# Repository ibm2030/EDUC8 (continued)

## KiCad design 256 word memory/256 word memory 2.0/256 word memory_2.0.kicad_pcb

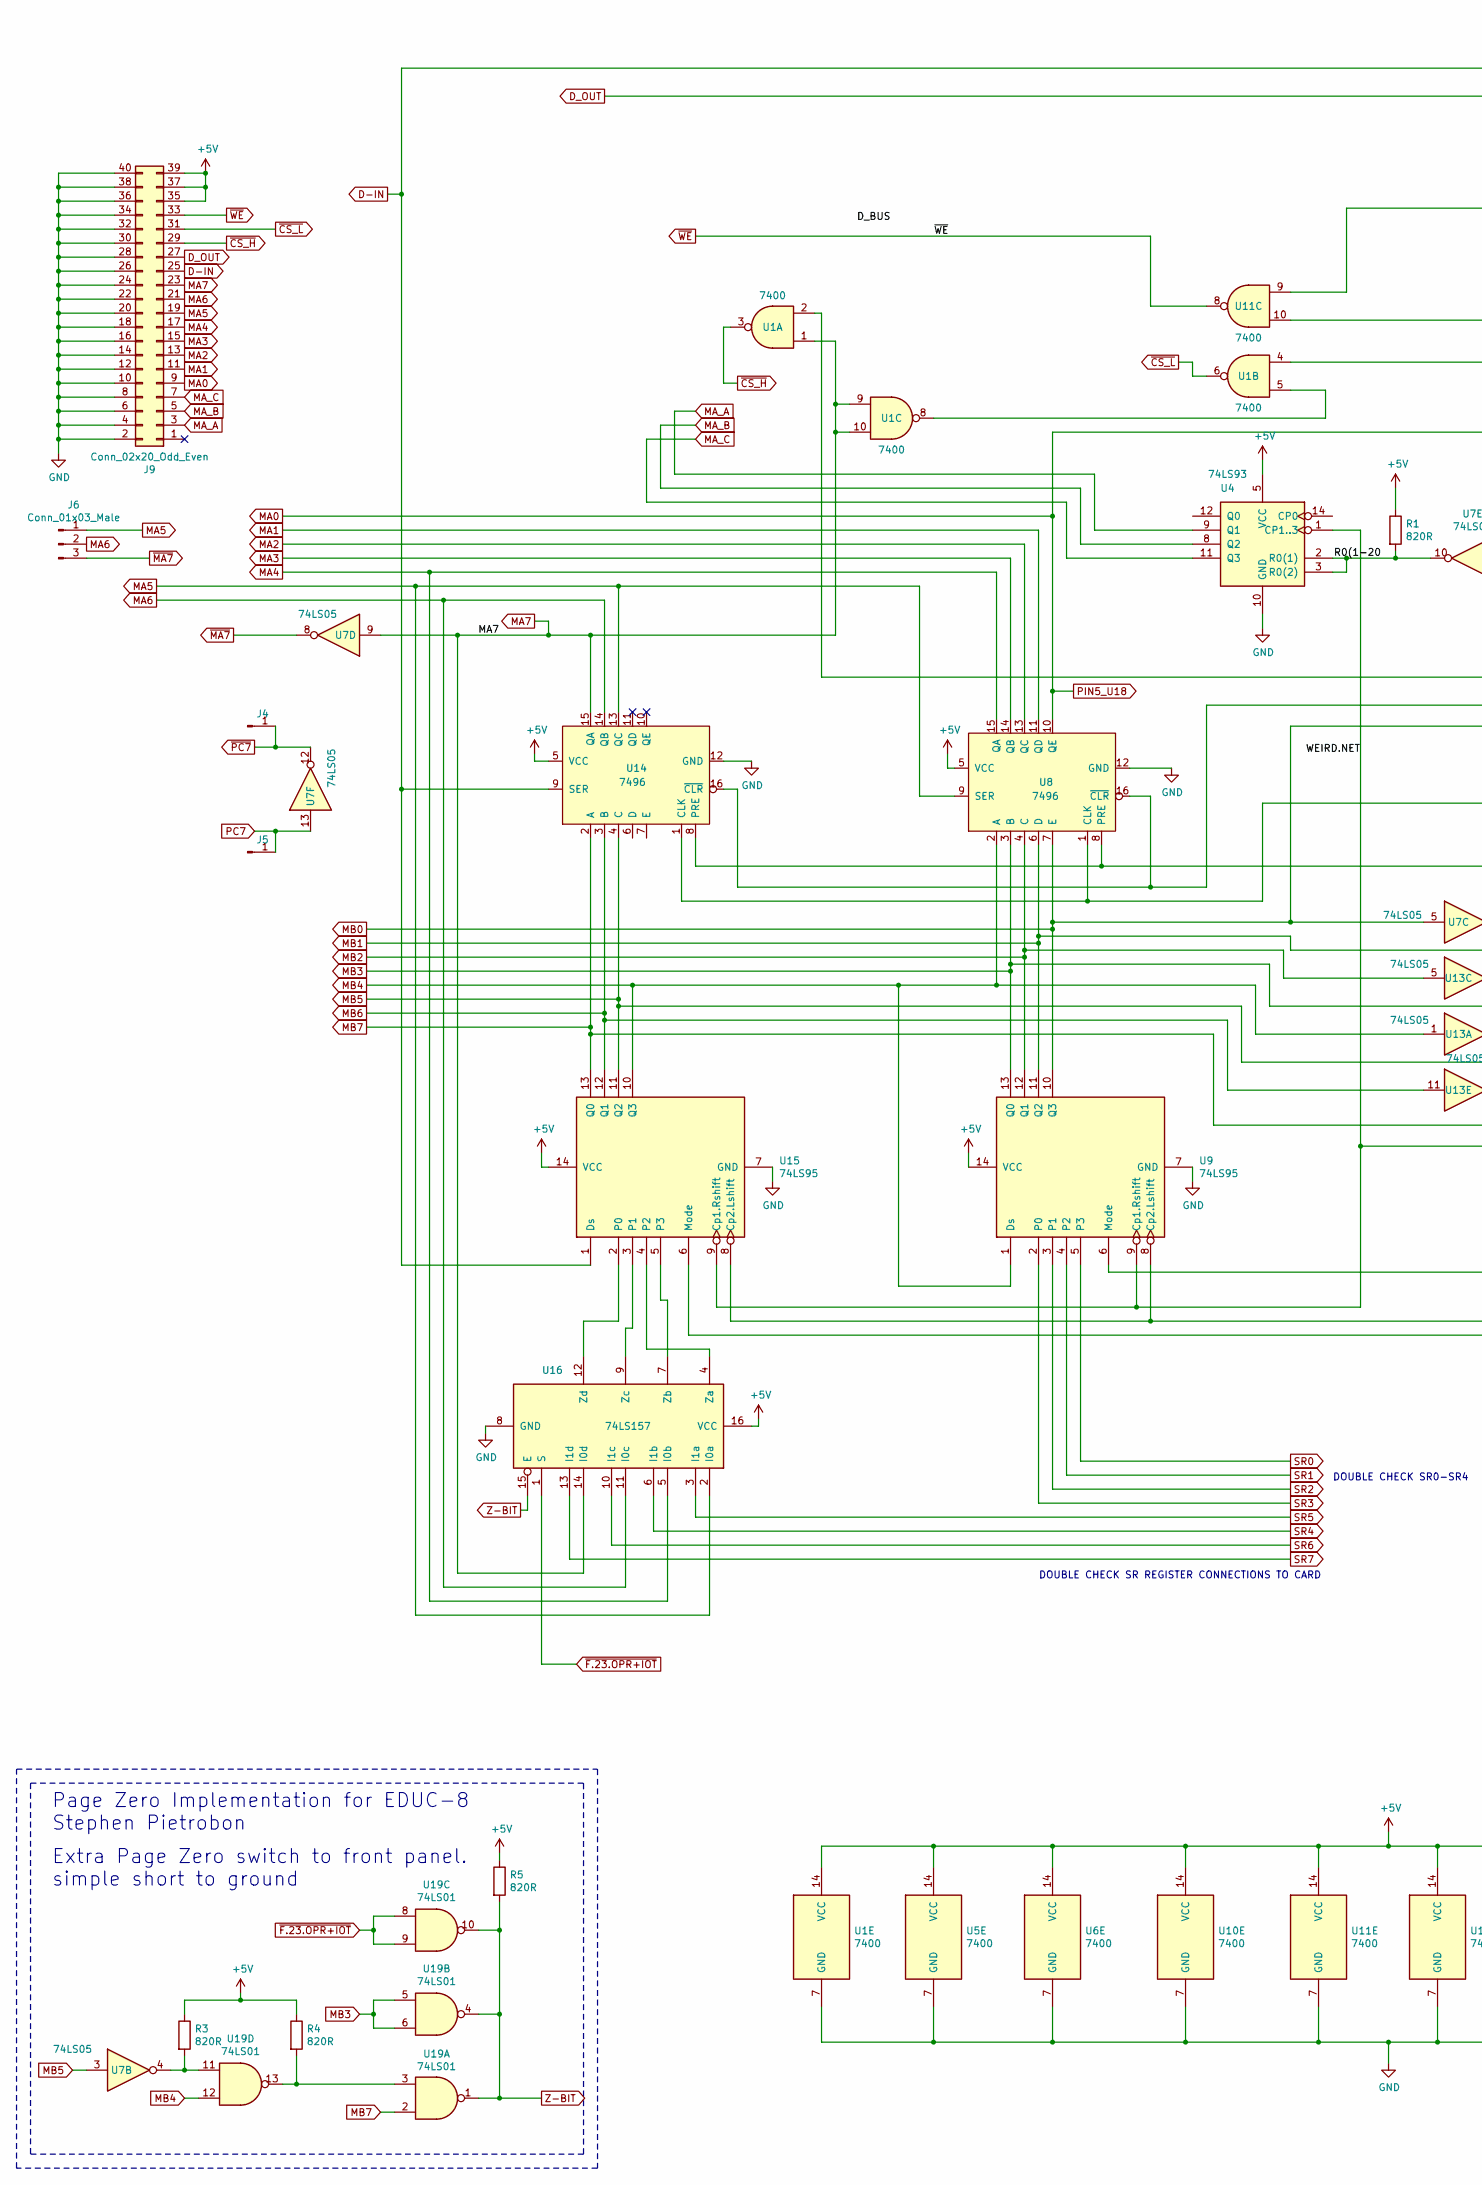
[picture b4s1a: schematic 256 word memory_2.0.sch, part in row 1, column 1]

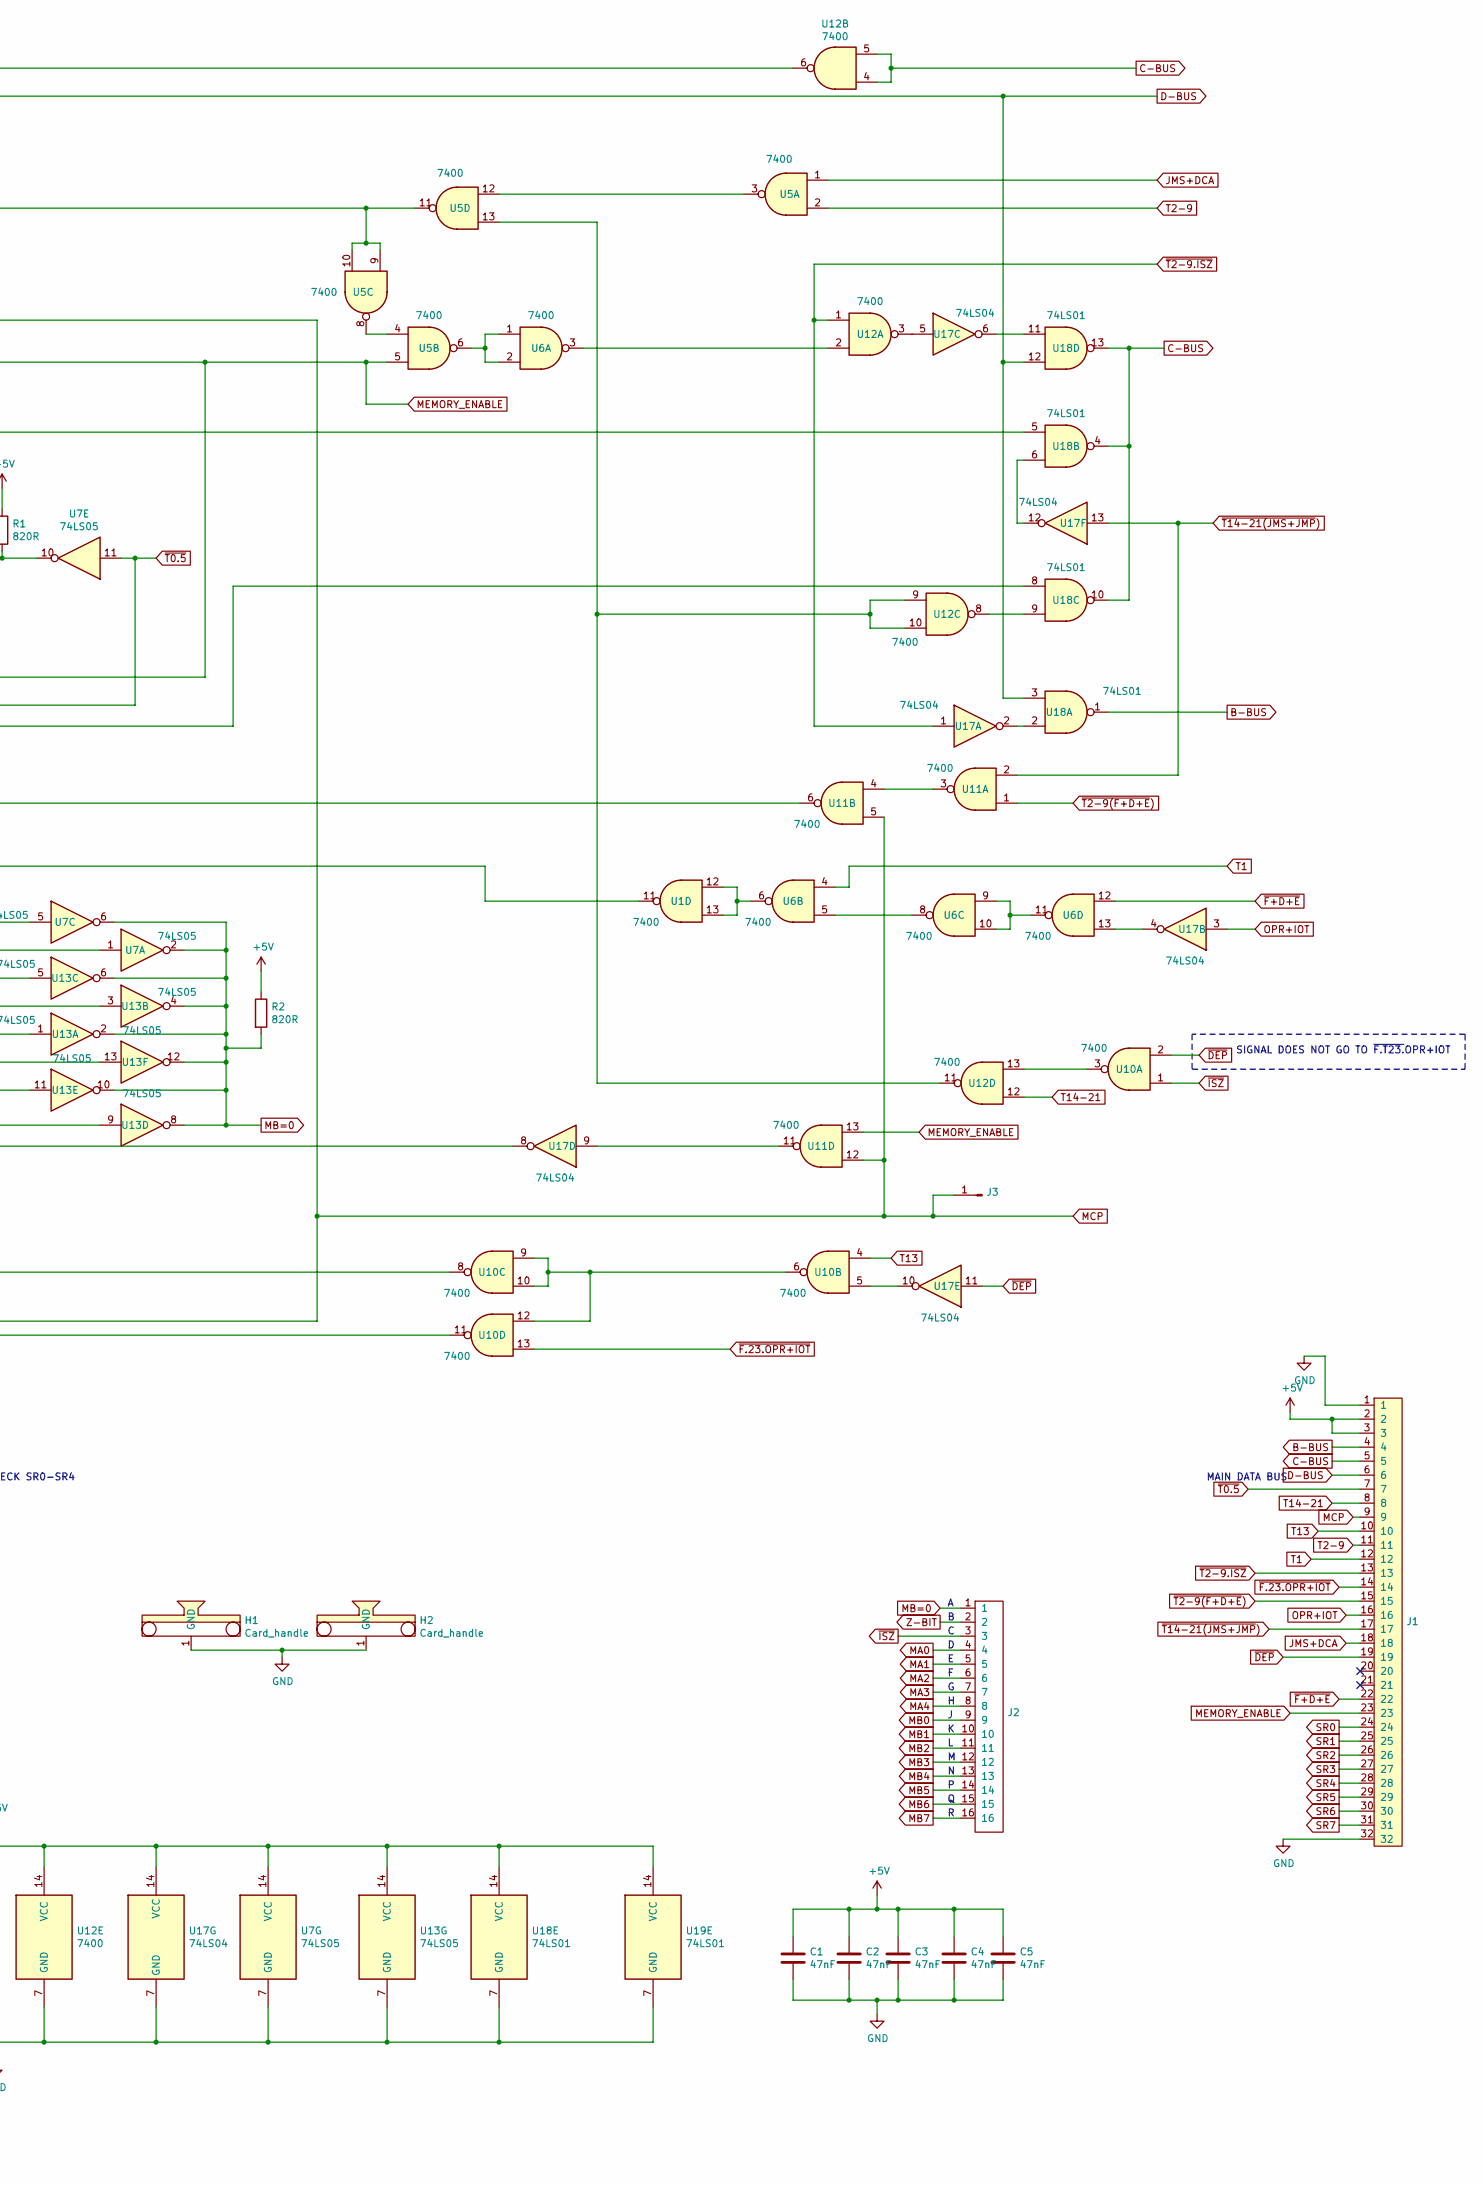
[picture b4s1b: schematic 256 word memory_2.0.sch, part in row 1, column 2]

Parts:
C1, C2, C3, C4, C5: 47nF; C_Disc_D5.0mm_W2.5mm_P5.00mm
H1, H2: Card_handle
J1: 32-way-pcb-edge-Educ-8-connectors; PCB_32pin
J2: 16-way-pcb-edge-Educ-8-connectors; PCB_16pin
J3, J4, J5: Conn_01x01_Male; Pin_D1.0mm_L10.0mm
J6: Conn_01x03_Male; PinHeader_1x03_P2.54mm_Horizontal
J9: Conn_02x20_Odd_Even; IDC-Header_2x20_P2.54mm_Horizontal
R1, R2, R3, R4, R5: 820R; R_Axial_DIN0207_L6.3mm_D2.5mm_P10.16mm_Horizontal
U1, U5, U6, U10, U11, U12: 7400; DIP-14_W7.62mm
U4: 74LS93; DIP-14_W7.62mm
U7, U13: 74LS05; DIP-14_W7.62mm
U8, U14: 7496; DIP-16_W7.62mm
U9, U15: 74LS95; DIP-14_W7.62mm
U16: 74LS157; DIP-16_W7.62mm
U17: 74LS04; DIP-14_W7.62mm
U18, U19: 74LS01; DIP-14_W7.62mm

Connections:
+5V: C1.1, C2.1, C3.1, C4.1, C5.1, J1.2, J1.3, J9.35, J9.37, J9.39, R1.1, R2.1, R3.1, R4.1, R5.1, U1.14 (VCC), U4.5 (VCC), U5.14 (VCC), U6.14 (VCC), U7.14 (VCC), U8.5 (VCC), U9.14 (VCC), U10.14 (VCC), U11.14 (VCC), U12.14 (VCC), U13.14 (VCC), U14.5 (VCC), U15.14 (VCC), U16.16 (VCC), U17.14 (VCC), U18.14 (VCC), U19.14 (VCC)
/R0(1-20: R1.2, U4.2 (R0(1)), U4.3 (R0(2)), U7.10
/WEIRD.NET: U4.1 (CP1..3), U9.9 (Cp1.Rshift), U15.9 (Cp1.Rshift), U17.8
B-BUS: J1.4, U18.1
C-BUS: J1.5, U12.4, U12.5, U18.4, U18.10, U18.13
D-BUS: J1.6, J9.27, U18.3, U18.12
D-IN: J9.25, U12.6, U14.9 (SER), U15.1 (Ds)
GND: C1.2, C2.2, C3.2, C4.2, C5.2, H1.1, H2.1, J1.1, J1.32, J9.2, J9.4, J9.6, J9.8, J9.10, J9.12, J9.14, J9.16, J9.18, J9.20, J9.22, J9.24, J9.26, J9.28, J9.30, J9.32, J9.34, J9.36, J9.38, J9.40, U1.7 (GND), U4.10 (GND), U5.7 (GND), U6.7 (GND), U7.7 (GND), U8.12 (GND), U9.7 (GND), U10.7 (GND), U11.7 (GND), U12.7 (GND), U13.7 (GND), U14.12 (GND), U15.7 (GND), U16.8 (GND), U17.7 (GND), U18.7 (GND), U19.7 (GND)
JMS+DCA: J1.18, U5.1
MA0: J2.4, J9.9, U8.10 (QE), U18.5
MA1: J2.5, J9.11, U8.11 (QD)
MA2: J2.6, J9.13, U8.13 (QC)
MA3: J2.7, J9.15, U8.14 (QB)
MA4: J2.8, J9.17, U8.15 (QA), U16.5 (I0b)
MA5: J6.1, J9.19, U8.9 (SER), U14.13 (QC), U16.2 (I0a)
MA6: J6.2, J9.21, U14.14 (QB), U16.11 (I0c)
MA7: J9.23, U1.1, U1.9, U1.10, U7.9, U14.15 (QA), U16.14 (I0d)
MA_A: J9.3, U4.9 (Q1)
MA_B: J9.5, U4.8 (Q2)
MA_C: J9.7, U4.11 (Q3)
MB0: J2.9, U7.5, U8.7 (E), U9.10 (Q3), U18.8
MB1: J2.10, U7.1, U8.6 (D), U9.11 (Q2)
MB2: J2.11, U8.4 (C), U9.12 (Q1), U13.5
MB3: J2.12, U8.3 (B), U9.13 (Q0), U13.3, U19.5, U19.6
MB4: J2.13, U8.2 (A), U9.1 (Ds), U13.1, U15.10 (Q3), U19.12
MB5: J2.14, U7.3, U13.13, U14.4 (C), U15.11 (Q2)
MB6: J2.15, U13.11, U14.3 (B), U15.12 (Q1)
MB7: J2.16, U13.9, U14.2 (A), U15.13 (Q0), U19.2
MB=0: J2.1, R2.2, U7.2, U7.6, U13.2, U13.4, U13.6, U13.8, U13.10, U13.12
MCP: J1.9, J3.1, U9.8 (Cp2.Lshift), U11.5, U11.10, U11.12, U15.8 (Cp2.Lshift)
MEMORY_ENABLE: J1.23, U1.2, U1.4, U5.5, U11.13
unnamed: R3.2, U7.4, U19.11
unnamed: R4.2, U19.3, U19.13
unnamed: U1.5, U1.8
unnamed: U1.11, U8.8 (PRE), U14.8 (PRE)
unnamed: U1.12, U1.13, U6.6
unnamed: U5.4, U5.8
unnamed: U5.6, U6.1, U6.2
unnamed: U5.3, U5.12
unnamed: U6.5, U6.8
unnamed: U6.9, U6.10, U6.11
unnamed: U10.3, U12.13
unnamed: U10.5, U17.10
unnamed: U9.6 (Mode), U10.8
unnamed: U10.6, U10.9, U10.10, U10.12
unnamed: U10.11, U15.6 (Mode)
unnamed: U11.3, U11.4
unnamed: U8.1 (CLK), U11.6, U14.1 (CLK)
unnamed: U5.9, U5.10, U5.11, U11.9
unnamed: U11.11, U17.9
unnamed: U6.3, U12.2
unnamed: U12.3, U17.5
unnamed: U12.8, U18.9
unnamed: U5.13, U12.9, U12.10, U12.11
unnamed: U15.2 (P0), U16.12 (Zd)
unnamed: U15.3 (P1), U16.9 (Zc)
unnamed: U15.4 (P2), U16.4 (Za)
unnamed: U15.5 (P3), U16.7 (Zb)
unnamed: U17.2, U18.2
unnamed: U6.13, U17.4
unnamed: U17.6, U18.11
unnamed: U17.12, U18.6
OPR+IOT: J1.16, U17.3
PC7: J5.1, U7.13
SR0: J1.24, U9.5 (P3)
SR1: J1.25, U9.4 (P2)
SR2: J1.26, U9.3 (P1)
SR3: J1.27, U9.2 (P0)
SR4: J1.28, U16.6 (I1b)
SR5: J1.29, U16.3 (I1a)
SR6: J1.30, U16.10 (I1c)
SR7: J1.31, U16.13 (I1d)
T1: J1.12, U6.4
T2-9: J1.11, U5.2
T13: J1.10, U10.4
T14-21: J1.8, U12.12
Z-BIT: J2.2, R5.2, U16.15 (E), U19.1, U19.4, U19.10
~CS_H: J9.29, U1.3
~CS_L: J9.31, U1.6
~DEP: J1.19, U10.2, U17.11
~F+D+E: J1.22, U6.12
~F.23.OPR+IOT: J1.14, U10.13, U16.1 (S), U19.8, U19.9
~ISZ: J2.3, U10.1
~MA7: J6.3, U7.8
~PC7: J4.1, U7.12
~T0.5: J1.7, U7.11, U8.16 (~CLR), U14.16 (~CLR)
~T2-9(F+D+E): J1.15, U11.1
~T2-9.ISZ: J1.13, U12.1, U17.1
~T14-21(JMS+JMP): J1.17, U11.2, U17.13
~WE: J9.33, U11.8

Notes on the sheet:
MAIN DATA BUS
DOUBLE CHECK SR REGISTER CONNECTIONS TO CARD
Page Zero Implementation for EDUC-8 Stephen Pietrobon
Extra Page Zero switch to front panel. simple short to ground
DOUBLE CHECK SR0-SR4
SIGNAL DOES NOT GO TO ~F.T23.~OPR+IOT

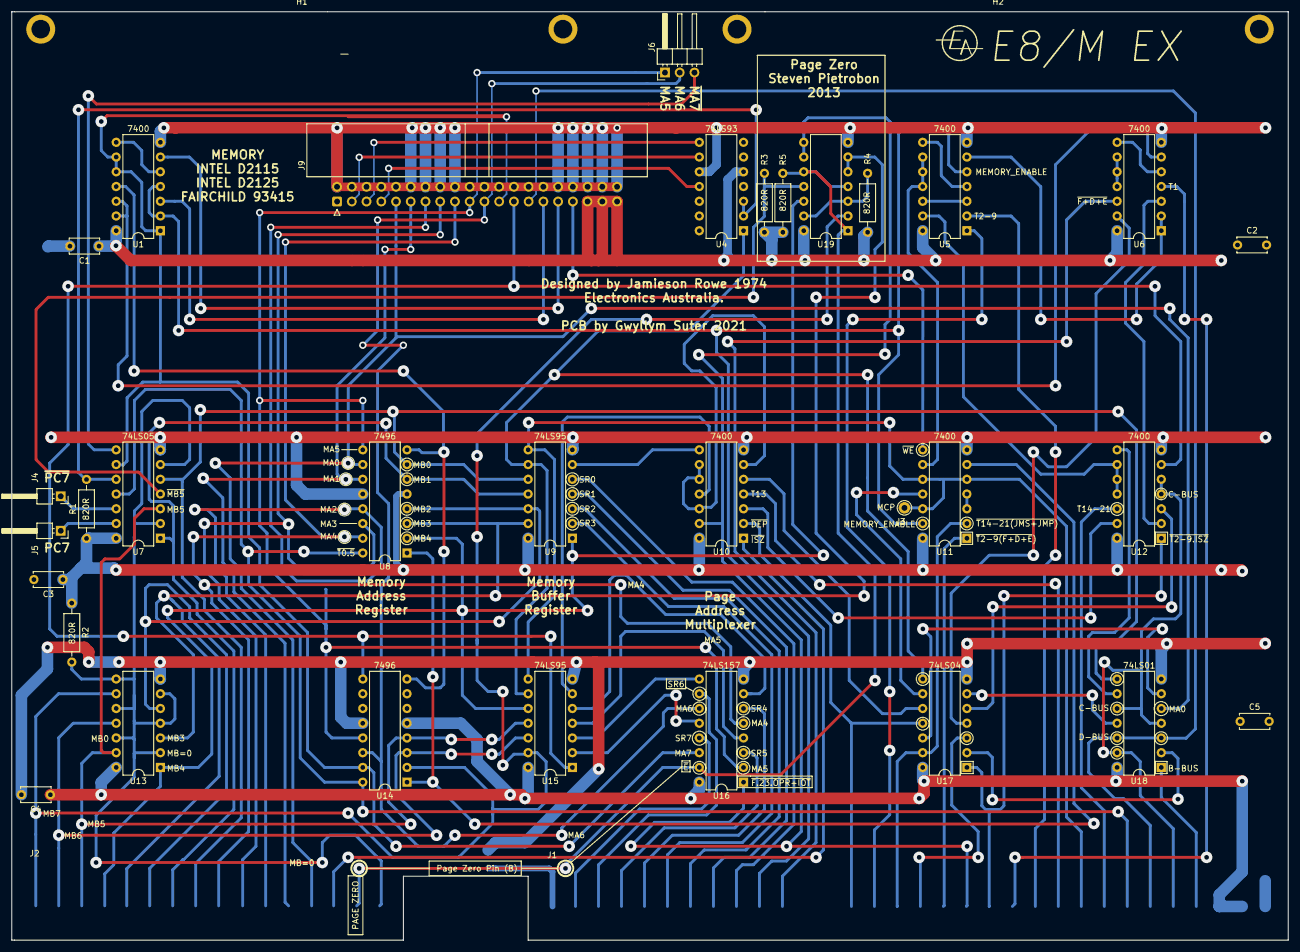
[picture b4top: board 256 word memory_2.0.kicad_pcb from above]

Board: 2 copper layers, 220.0 x 160.0 mm, 36 parts (0 on the bottom side), 90 nets.

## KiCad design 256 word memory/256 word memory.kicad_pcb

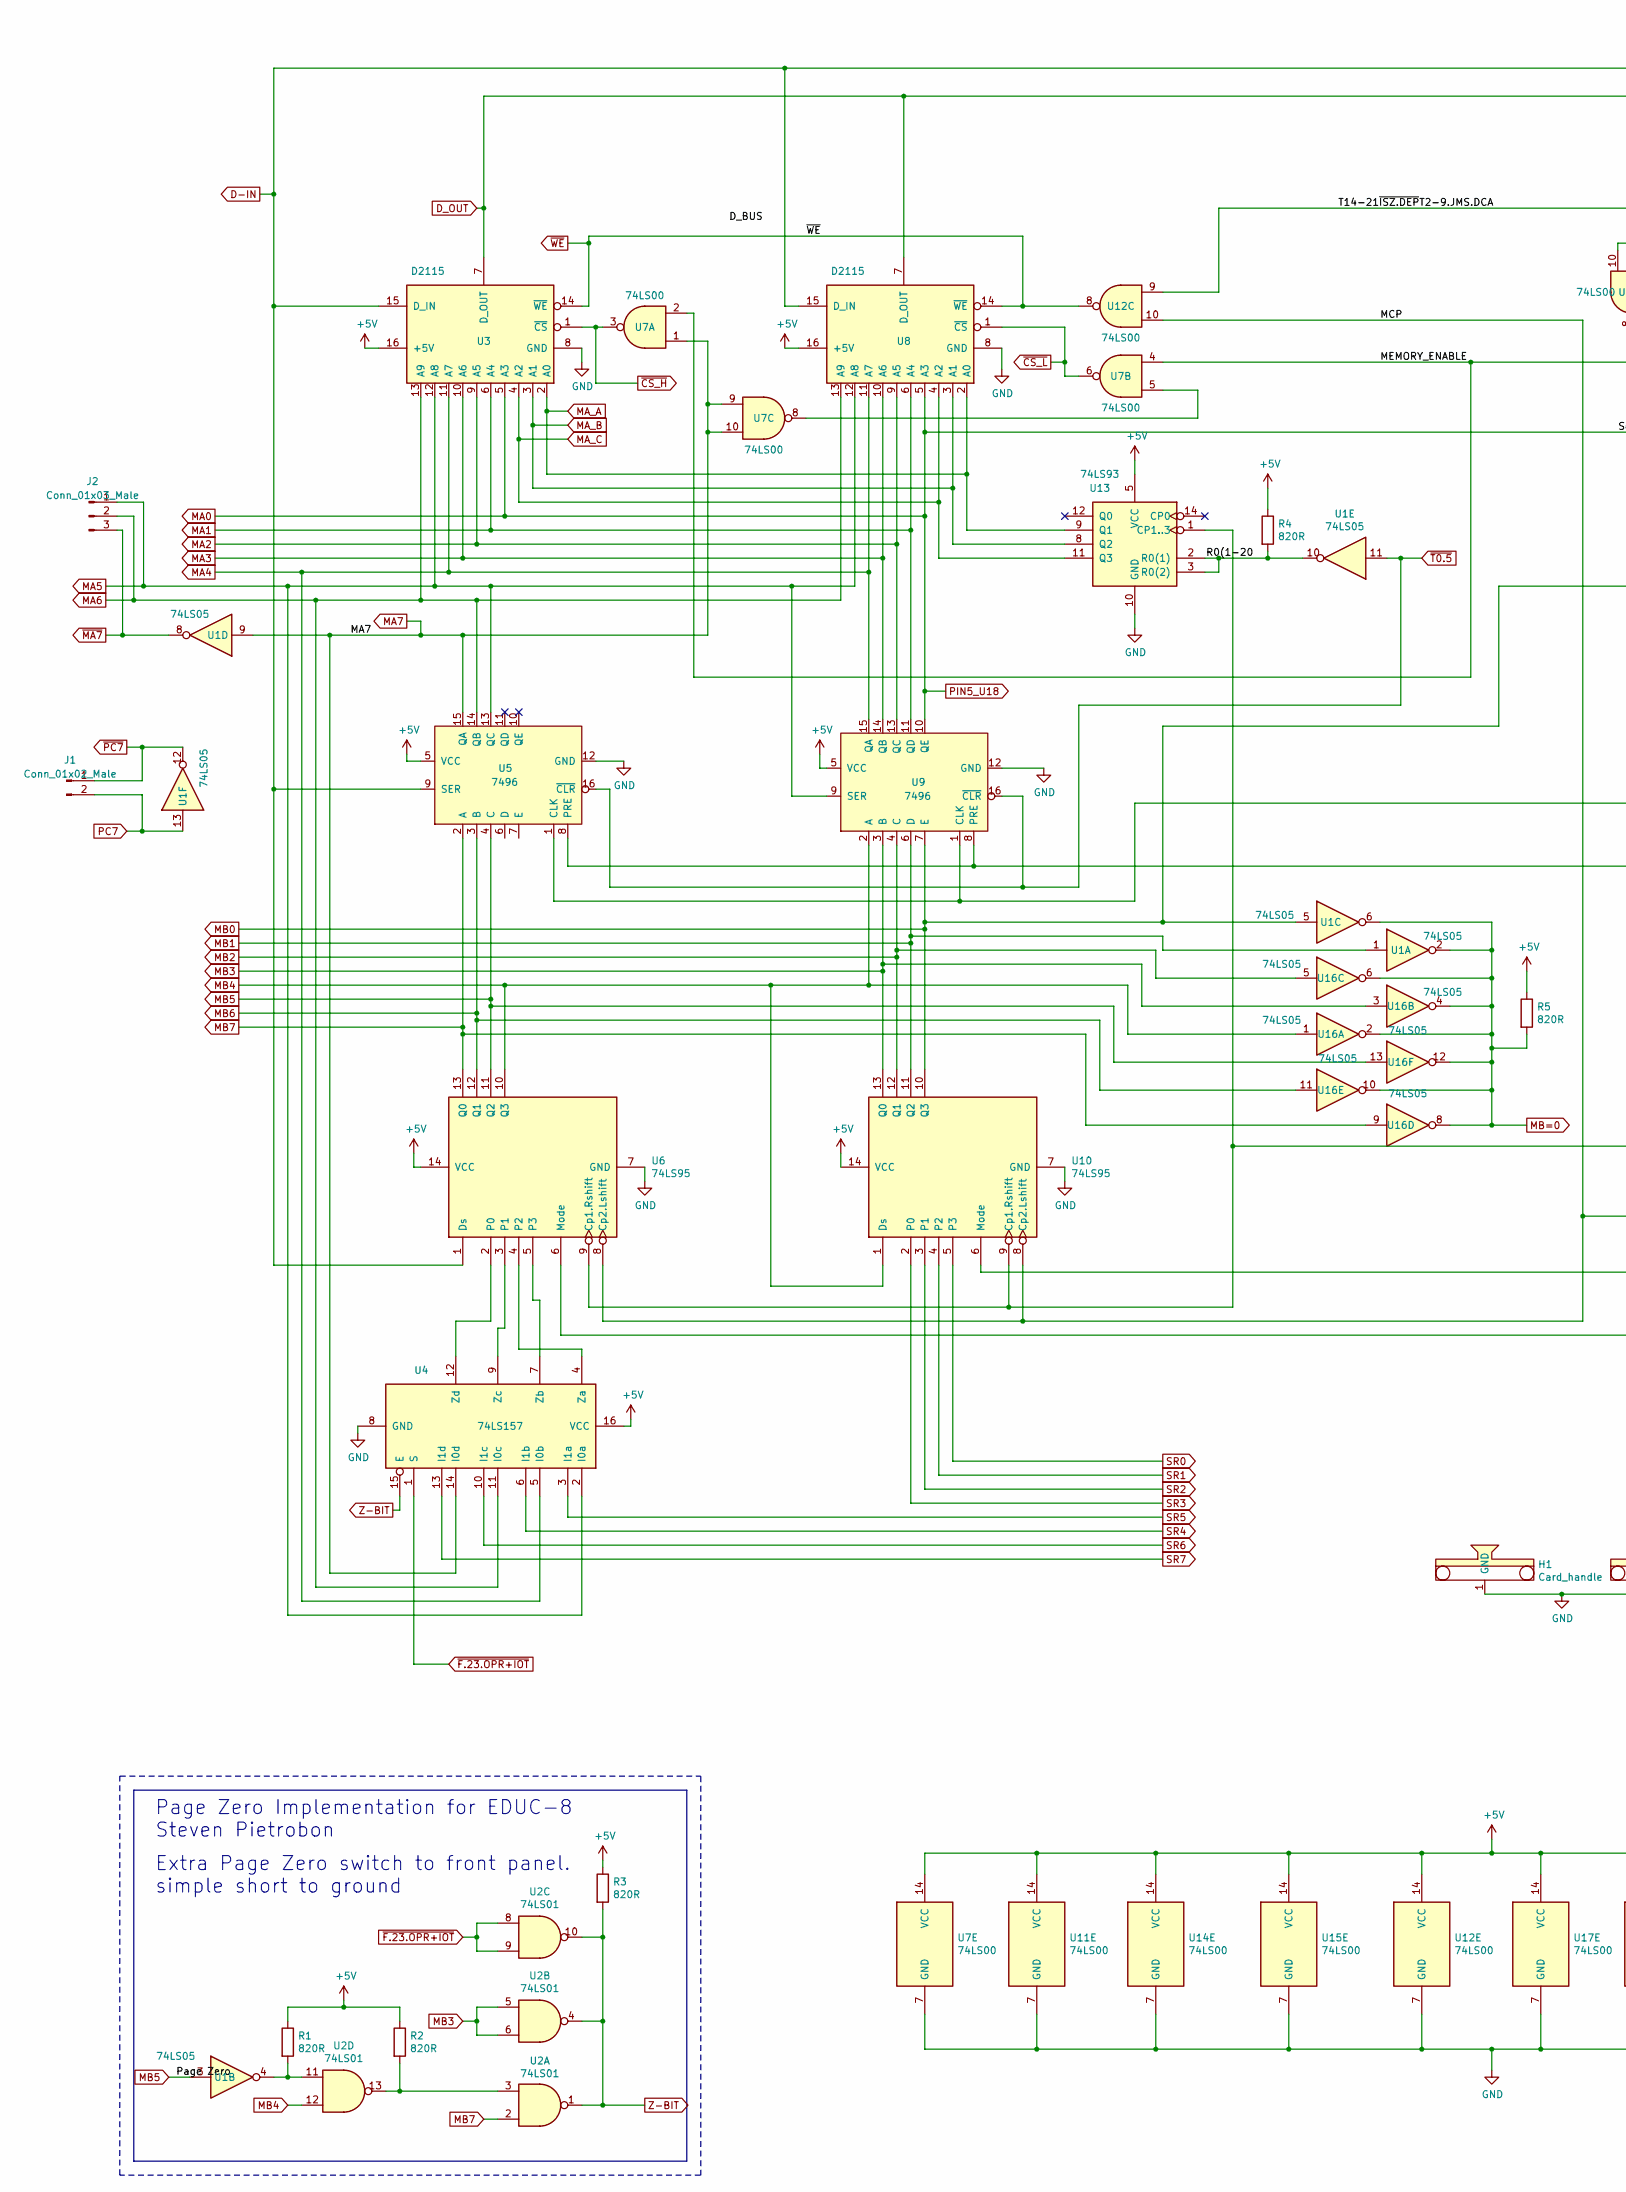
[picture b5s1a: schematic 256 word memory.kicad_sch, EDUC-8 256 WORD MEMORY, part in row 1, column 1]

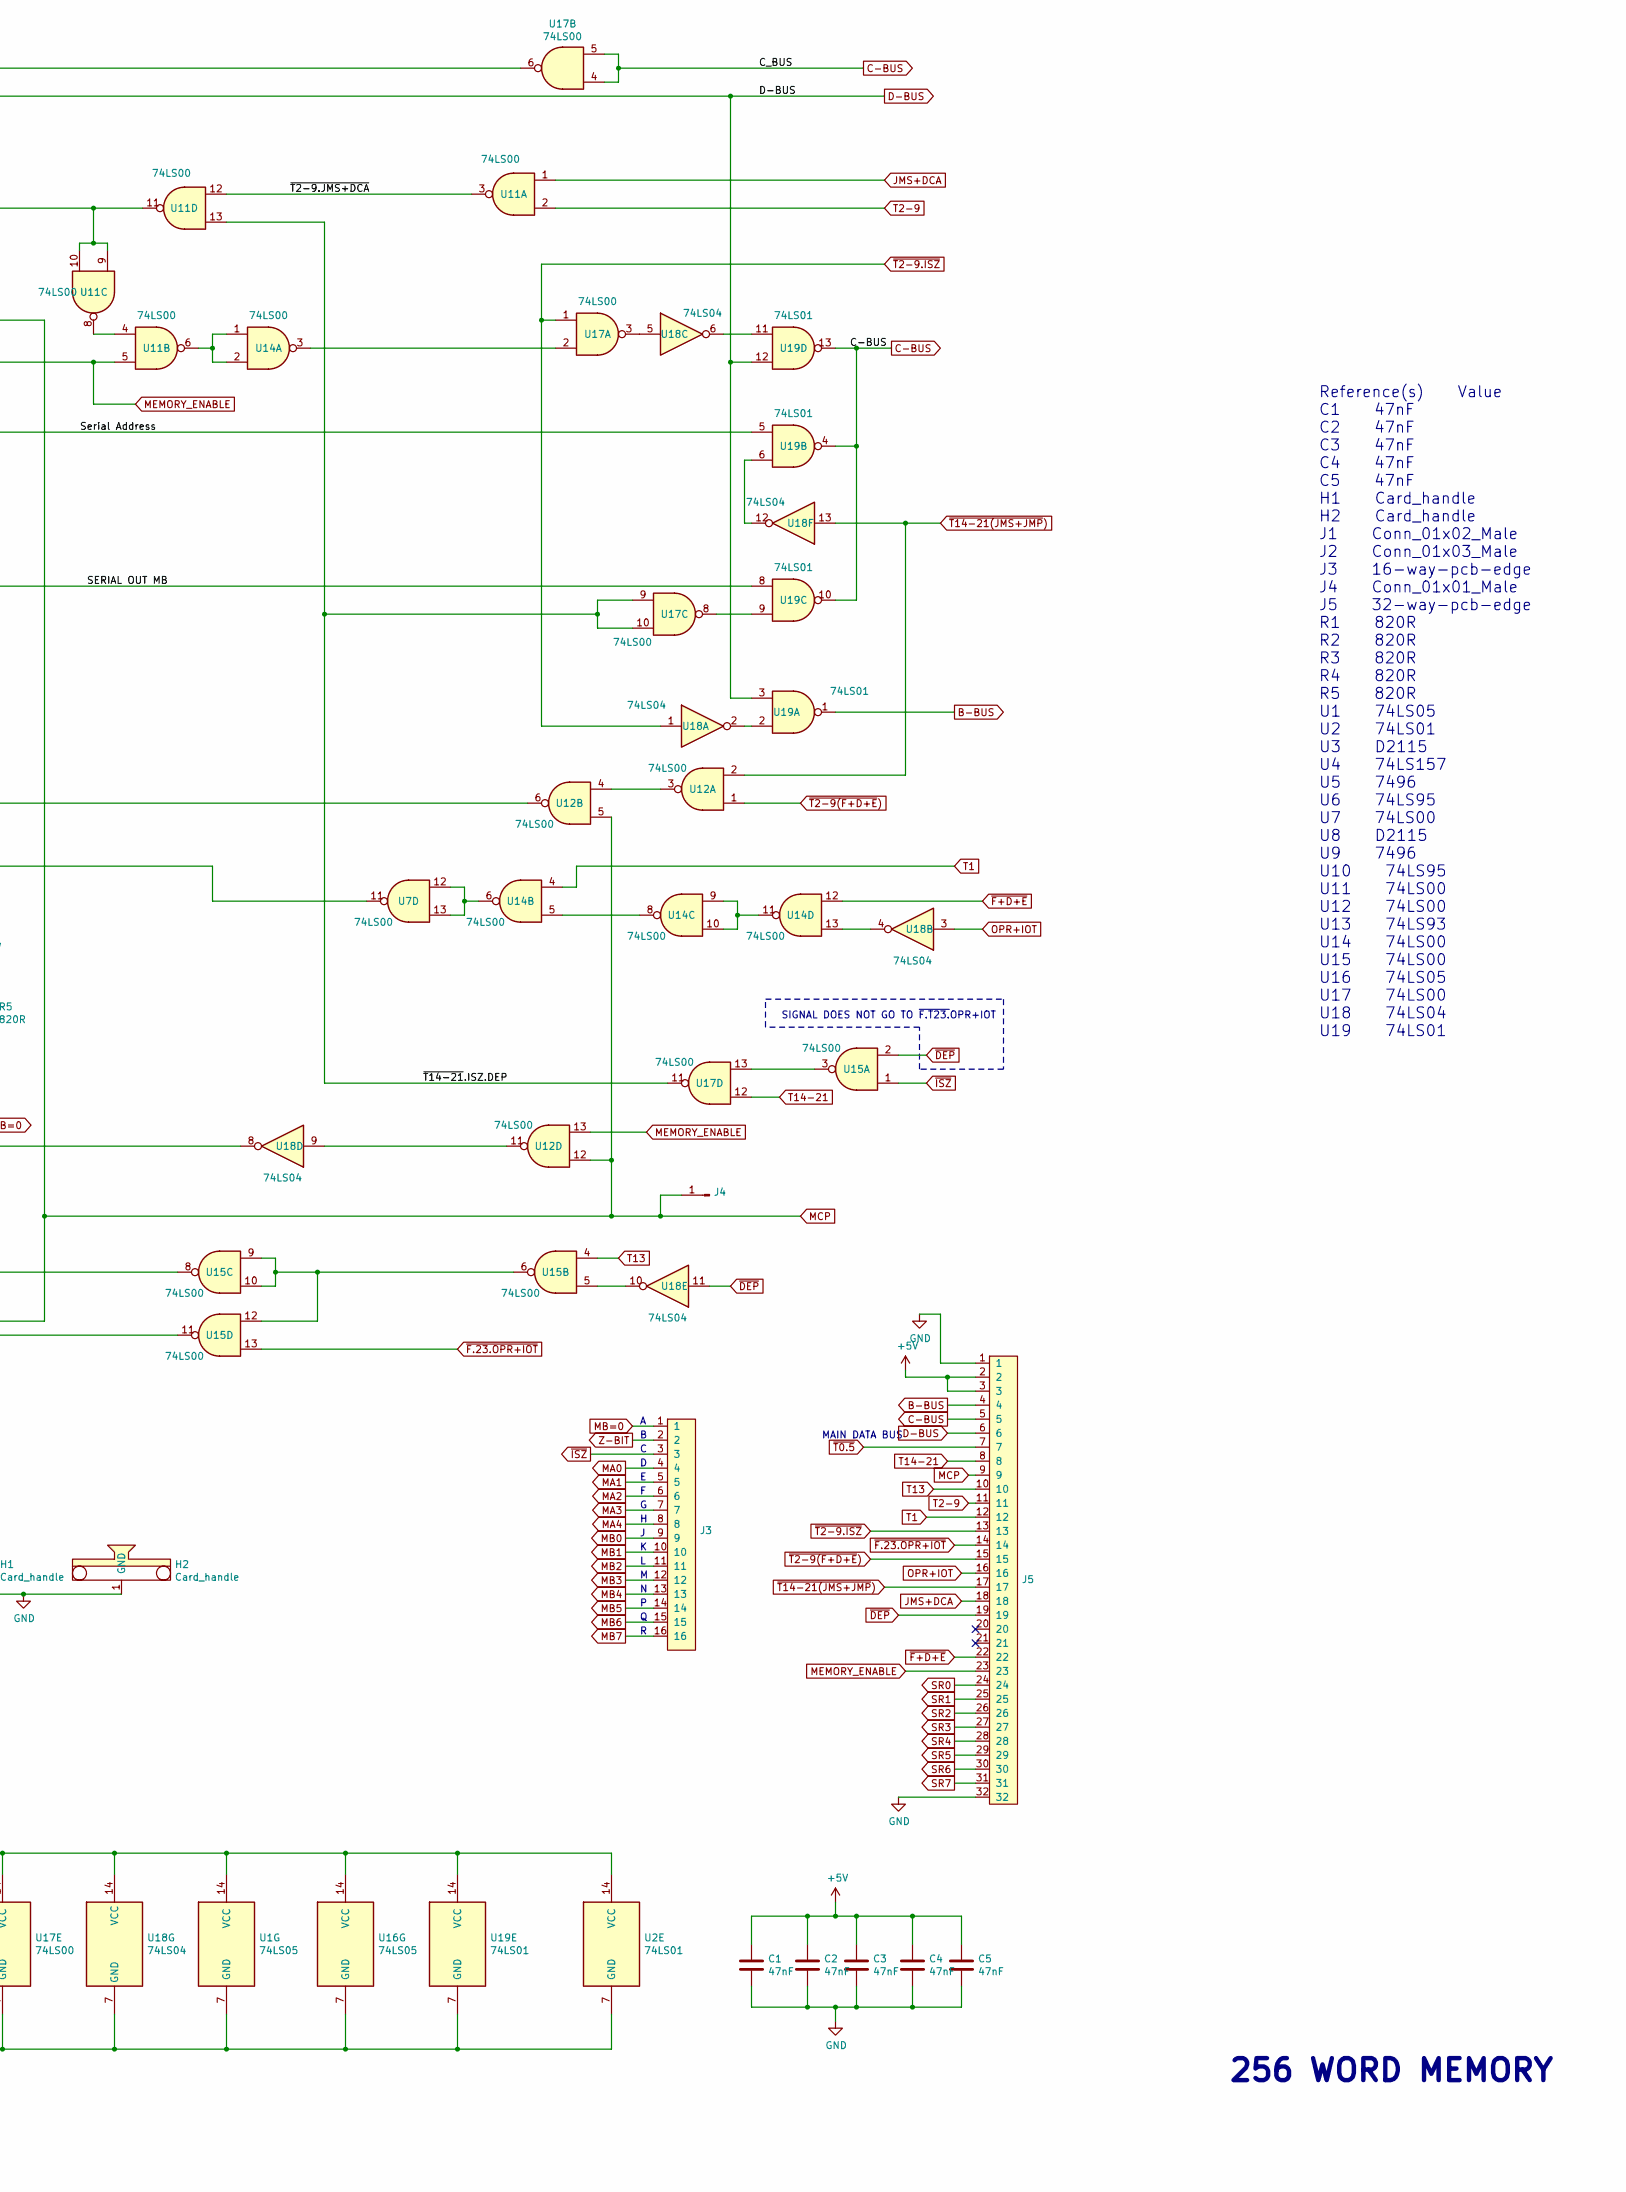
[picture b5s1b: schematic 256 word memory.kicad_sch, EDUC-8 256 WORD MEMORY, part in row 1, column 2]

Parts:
C1, C2, C3, C4, C5: 47nF; C_Disc_D5.0mm_W2.5mm_P5.00mm
H1, H2: Card_handle
J1: Conn_01x02_Male; JST_XH_S2B-XH-A_1x02_P2.50mm_Horizontal
J2: Conn_01x03_Male; JST_XH_S3B-XH-A_1x03_P2.50mm_Horizontal
J3: 16-way-pcb-edge-Educ-8-connectors; PCB_16pin
J4: Conn_01x01_Male; Pin_D1.0mm_L10.0mm
J5: 32-way-pcb-edge-Educ-8-connectors; PCB_32pin
R1, R2, R3, R4, R5: 820R; R_Axial_DIN0207_L6.3mm_D2.5mm_P10.16mm_Horizontal
U1, U16: 74LS05; DIP-14_W7.62mm
U2, U19: 74LS01; DIP-14_W7.62mm
U3, U8: D2115; DIP-16_W7.62mm
U4: 74LS157; DIP-16_W7.62mm
U5, U9: 7496; DIP-16_W7.62mm
U6, U10: 74LS95; DIP-14_W7.62mm
U7, U11, U12, U14, U15, U17: 74LS00; DIP-14_W7.62mm
U13: 74LS93; DIP-14_W7.62mm
U18: 74LS04; DIP-14_W7.62mm

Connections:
+5V: C1.1, C2.1, C3.1, C4.1, C5.1, J5.2, J5.3, R1.1, R2.1, R3.1, R4.1, R5.1, U1.14 (VCC), U2.14 (VCC), U3.16 (+5V), U4.16 (VCC), U5.5 (VCC), U6.14 (VCC), U7.14 (VCC), U8.16 (+5V), U9.5 (VCC), U10.14 (VCC), U11.14 (VCC), U12.14 (VCC), U13.5 (VCC), U14.14 (VCC), U15.14 (VCC), U16.14 (VCC), U17.14 (VCC), U18.14 (VCC), U19.14 (VCC)
/R0(1-20: R4.2, U1.10, U13.2 (R0(1)), U13.3 (R0(2))
/T14-21~ISZ.DEPT2-9.JMS.DCA: U11.9, U11.10, U11.11, U12.9
/~T2-9.JMS+DCA: U11.3, U11.12
/~T14-21.ISZ.DEP: U11.13, U17.9, U17.10, U17.11
B-BUS: J5.4, U19.1
C-BUS: J5.5, U17.4, U17.5, U19.4, U19.10, U19.13
D-BUS: J5.6, U3.7 (D_OUT), U8.7 (D_OUT), U19.3, U19.12
D-IN: U3.15 (D_IN), U5.9 (SER), U6.1 (Ds), U8.15 (D_IN), U17.6
GND: C1.2, C2.2, C3.2, C4.2, C5.2, H1.1 (GND), H2.1 (GND), J5.1, J5.32, U1.7 (GND), U2.7 (GND), U3.8 (GND), U4.8 (GND), U5.12 (GND), U6.7 (GND), U7.7 (GND), U8.8 (GND), U9.12 (GND), U10.7 (GND), U11.7 (GND), U12.7 (GND), U13.10 (GND), U14.7 (GND), U15.7 (GND), U16.7 (GND), U17.7 (GND), U18.7 (GND), U19.7 (GND)
JMS+DCA: J5.18, U11.1
MA0: J3.4, U3.5 (A3), U8.5 (A3), U9.10 (QE), U19.5
MA1: J3.5, U3.6 (A4), U8.6 (A4), U9.11 (QD)
MA2: J3.6, U3.9 (A5), U8.9 (A5), U9.13 (QC)
MA3: J3.7, U3.10 (A6), U8.10 (A6), U9.14 (QB)
MA4: J3.8, U3.11 (A7), U4.5 (I0b), U8.11 (A7), U9.15 (QA)
MA5: J2.1, U3.12 (A8), U4.2 (I0a), U5.13 (QC), U8.12 (A8), U9.9 (SER)
MA6: J2.2, U3.13 (A9), U4.11 (I0c), U5.14 (QB), U8.13 (A9)
MA7: U1.9, U4.14 (I0d), U5.15 (QA), U7.1, U7.9, U7.10
MA_A: U3.2 (A0), U8.2 (A0), U13.9 (Q1)
MA_B: U3.3 (A1), U8.3 (A1), U13.8 (Q2)
MA_C: U3.4 (A2), U8.4 (A2), U13.11 (Q3)
MB0: J3.9, U1.5, U9.7 (E), U10.10 (Q3), U19.8
MB1: J3.10, U1.1, U9.6 (D), U10.11 (Q2)
MB2: J3.11, U9.4 (C), U10.12 (Q1), U16.5
MB3: J3.12, U2.5, U2.6, U9.3 (B), U10.13 (Q0), U16.3
MB4: J3.13, U2.12, U6.10 (Q3), U9.2 (A), U10.1 (Ds), U16.1
MB5: J3.14, U1.3, U5.4 (C), U6.11 (Q2), U16.13
MB6: J3.15, U5.3 (B), U6.12 (Q1), U16.11
MB7: J3.16, U2.2, U5.2 (A), U6.13 (Q0), U16.9
MB=0: J3.1, R5.2, U1.2, U1.6, U16.2, U16.4, U16.6, U16.8, U16.10, U16.12
MCP: J4.1, J5.9, U6.8 (Cp2.Lshift), U10.8 (Cp2.Lshift), U12.5, U12.10, U12.12
MEMORY_ENABLE: J5.23, U7.2, U7.4, U11.5, U12.13
unnamed: R1.2, U1.4, U2.11
unnamed: R2.2, U2.3, U2.13
unnamed: U4.4 (Za), U6.4 (P2)
unnamed: U4.7 (Zb), U6.5 (P3)
unnamed: U4.9 (Zc), U6.3 (P1)
unnamed: U4.12 (Zd), U6.2 (P0)
unnamed: U5.1 (CLK), U9.1 (CLK), U12.6
unnamed: U5.8 (PRE), U7.11, U9.8 (PRE)
unnamed: U6.6 (Mode), U15.11
unnamed: U7.5, U7.8
unnamed: U6.9 (Cp1.Rshift), U10.9 (Cp1.Rshift), U13.1 (CP1..3), U18.8
unnamed: U10.6 (Mode), U15.8
unnamed: U11.4, U11.8
unnamed: U11.6, U14.1, U14.2
unnamed: U12.3, U12.4
unnamed: U12.11, U18.9
unnamed: U14.3, U17.2
unnamed: U14.5, U14.8
unnamed: U7.12, U7.13, U14.6
unnamed: U14.9, U14.10, U14.11
unnamed: U14.13, U18.4
unnamed: U15.3, U17.13
unnamed: U15.5, U18.10
unnamed: U15.6, U15.9, U15.10, U15.12
unnamed: U17.3, U18.5
unnamed: U17.8, U19.9
unnamed: U18.2, U19.2
unnamed: U18.6, U19.11
unnamed: U18.12, U19.6
OPR+IOT: J5.16, U18.3
PC7: J1.2, U1.13
SR0: J5.24, U10.5 (P3)
SR1: J5.25, U10.4 (P2)
SR2: J5.26, U10.3 (P1)
SR3: J5.27, U10.2 (P0)
SR4: J5.28, U4.6 (I1b)
SR5: J5.29, U4.3 (I1a)
SR6: J5.30, U4.10 (I1c)
SR7: J5.31, U4.13 (I1d)
T1: J5.12, U14.4
T2-9: J5.11, U11.2
T13: J5.10, U15.4
T14-21: J5.8, U17.12
Z-BIT: J3.2, R3.2, U2.1, U2.4, U2.10, U4.15 (E)
~CS_H: U3.1 (~CS), U7.3
~CS_L: U7.6, U8.1 (~CS)
~DEP: J5.19, U15.2, U18.11
~F+D+E: J5.22, U14.12
~F.23.OPR+IOT: J5.14, U2.8, U2.9, U4.1 (S), U15.13
~ISZ: J3.3, U15.1
~MA7: J2.3, U1.8
~PC7: J1.1, U1.12
~T0.5: J5.7, U1.11, U5.16 (~CLR), U9.16 (~CLR)
~T2-9(F+D+E): J5.15, U12.1
~T2-9.ISZ: J5.13, U17.1, U18.1
~T14-21(JMS+JMP): J5.17, U12.2, U18.13
~WE: U3.14 (~WE), U8.14 (~WE), U12.8

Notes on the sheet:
SIGNAL DOES NOT GO TO ~{F.T23.}OPR+IOT
Extra Page Zero switch to front panel. simple short to ground
Reference(s) Value C1 47nF C2 47nF C3 47nF C4 47nF C5 47nF H1 Card_handle H2 Card_handle J1 Conn_01x02_Male J2 Conn_01x03_Male J3 16-way-pcb-edge J4 Conn_01x01_Male J5 32-way-pcb-edge R1 820R R2 820R R3 820R R4 820R R5 820R U1 74LS05 U2 74LS01 U3 D2115 U4 74LS157 U5 7496 U6 74LS95 U7 74LS00 U8 D211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
Page Zero Implementation for EDUC-8 Steven Pietrobon
256 WORD MEMORY
MAIN DATA BUS

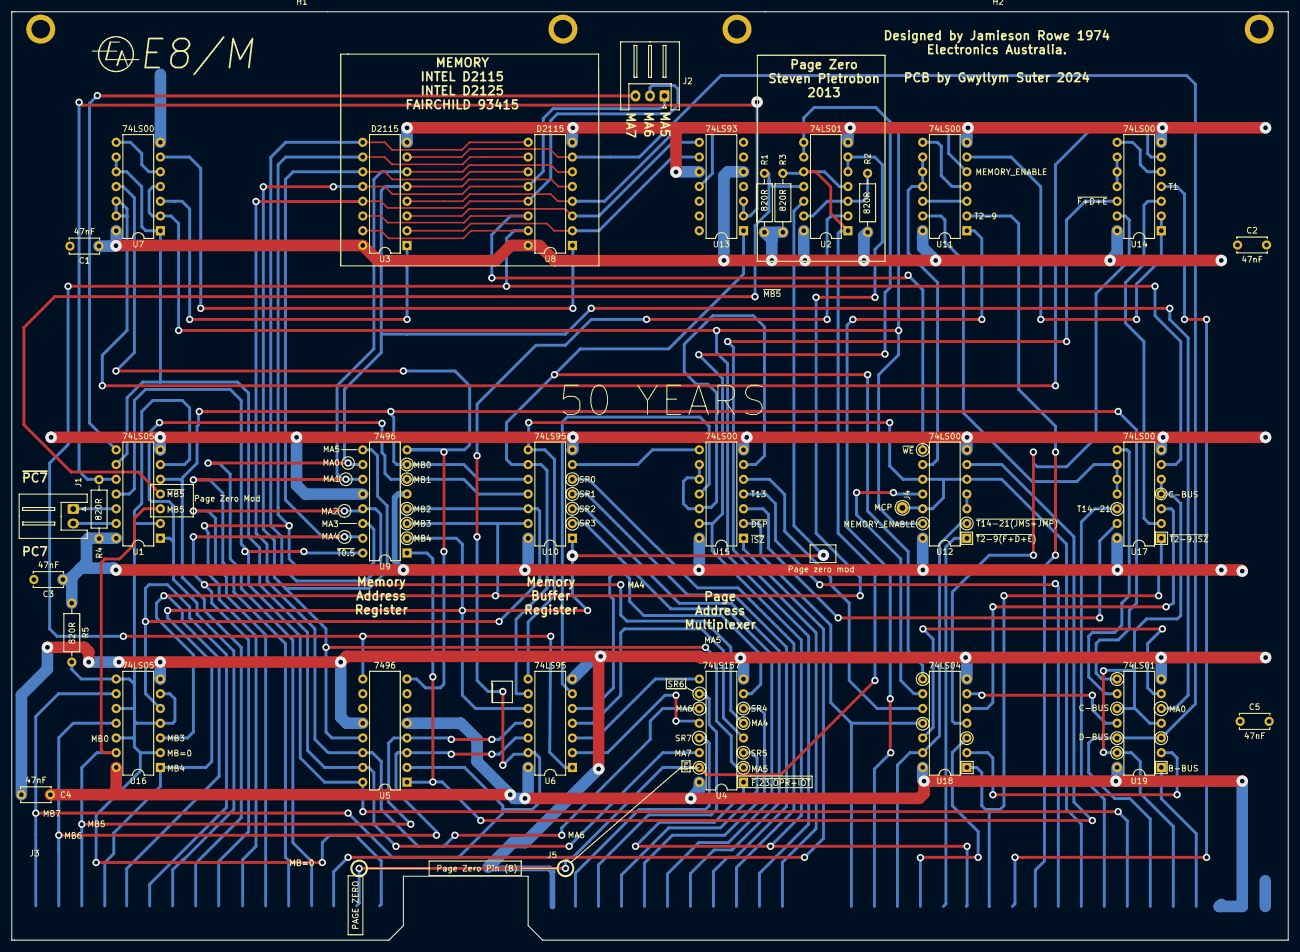
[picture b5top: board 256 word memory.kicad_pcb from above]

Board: 2 copper layers, 220.0 x 160.0 mm, 36 parts (0 on the bottom side), 90 nets.
